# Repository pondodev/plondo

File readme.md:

# plondo

a plaid inspired 4x12 ortholinear keyboard with a rotary encoder and oled panel.

building plondo? then start at the [BOM](docs/1-bom.md)!

this is a work in progress by me, someone who is a software engineer and very much not qualified to do this kind of
thing. i'm going to do it anyway.

if you're missing symbols/footprints then make sure you run `git submodule init && git submodule update` to pull the
relevant libraries down.

this keyboard derives from the [plaid](https://github.com/hsgw/plaid) and the
[mysterium](https://github.com/coseyfannitutti/mysterium).

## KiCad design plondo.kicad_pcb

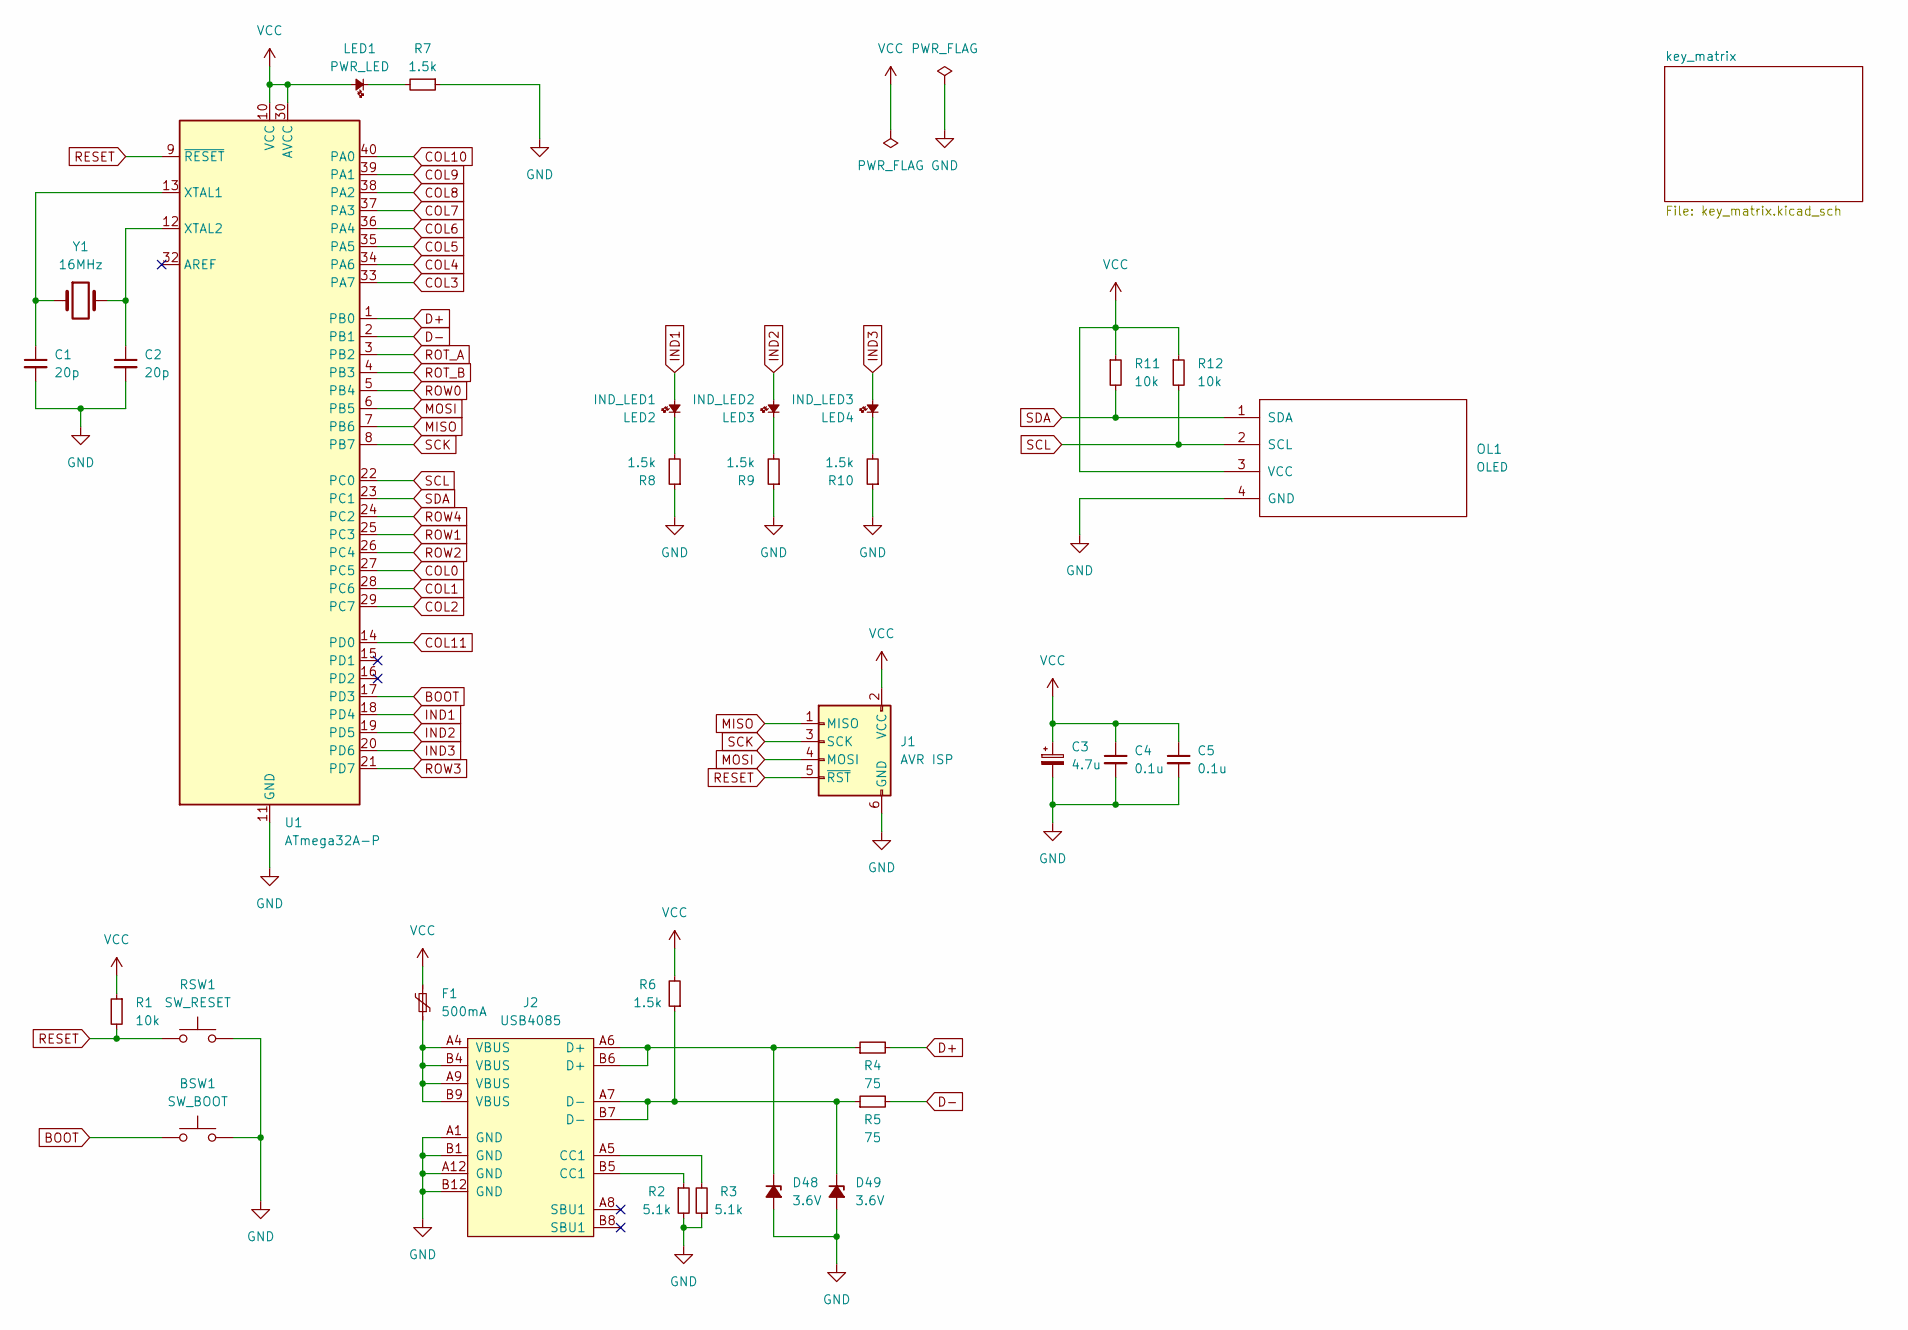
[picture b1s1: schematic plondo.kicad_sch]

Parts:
BSW1: SW_BOOT; SW_PUSH_6mm_H4.3mm
C1, C2: 20p; C_Disc_D7.5mm_W4.4mm_P5.00mm
C3: 4.7u; CP_Radial_D4.0mm_P1.50mm
C4, C5: 0.1u; C_Disc_D5.0mm_W2.5mm_P5.00mm
D48, D49: 3.6V; D_DO-35_SOD27_P7.62mm_Horizontal
F1: 500mA; Fuse_Littelfuse_395Series
J1: AVR ISP; PinHeader_2x03_P2.54mm_Vertical
J2: USB4085; Farnell 2924867
LED1: PWR_LED; LED_D3.0mm
LED2: IND_LED1; LED_D3.0mm
LED3: IND_LED2; LED_D3.0mm
LED4: IND_LED3; LED_D3.0mm
OL1: OLED; OLED_v2
R1, R11, R12: 10k; R_Axial_DIN0207_L6.3mm_D2.5mm_P7.62mm_Horizontal
R2, R3: 5.1k; R_Axial_DIN0207_L6.3mm_D2.5mm_P7.62mm_Horizontal
R4, R5: 75; R_Axial_DIN0207_L6.3mm_D2.5mm_P7.62mm_Horizontal
R6, R7, R8, R9, R10: 1.5k; R_Axial_DIN0207_L6.3mm_D2.5mm_P7.62mm_Horizontal
RSW1: SW_RESET; SW_PUSH_6mm_H4.3mm
U1: ATmega32A-P; DIP-40_W15.24mm_Socket
Y1: 16MHz; Resonator-2Pin_W10.0mm_H5.0mm

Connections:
BOOT: BSW1.1, U1.17 (PD3)
COL0: U1.27 (PC5); also elsewhere on the board
COL1: U1.28 (PC6); also elsewhere on the board
COL2: U1.29 (PC7); also elsewhere on the board
COL3: U1.33 (PA7); also elsewhere on the board
COL4: U1.34 (PA6); also elsewhere on the board
COL5: U1.35 (PA5); also elsewhere on the board
COL6: U1.36 (PA4); also elsewhere on the board
COL7: U1.37 (PA3); also elsewhere on the board
COL8: U1.38 (PA2); also elsewhere on the board
COL9: U1.39 (PA1); also elsewhere on the board
COL10: U1.40 (PA0); also elsewhere on the board
COL11: U1.14 (PD0); also elsewhere on the board
D+: R4.2, U1.1 (PB0)
D-: R5.2, U1.2 (PB1)
GND: BSW1.2, C1.2, C2.2, C3.2, C4.2, C5.2, D48.2 (A), D49.2 (A), J1.6 (GND), J2.A1 (GND), J2.A12 (GND), J2.B1 (GND), J2.B12 (GND), OL1.4 (GND), R2.2, R3.1, R7.1, R8.1, R9.1, R10.1, RSW1.2, U1.11 (GND), U1.31 (GND); also elsewhere on the board
IND1: LED2.2, U1.18 (PD4)
IND2: LED3.2, U1.19 (PD5)
IND3: LED4.2, U1.20 (PD6)
MISO: J1.1 (MISO), U1.7 (PB6)
MOSI: J1.4 (MOSI), U1.6 (PB5)
unnamed: C1.1, U1.13 (XTAL1), Y1.1
unnamed: C2.1, U1.12 (XTAL2), Y1.2
unnamed: D48.1 (K), J2.A6 (D+), J2.B6 (D+), R4.1
unnamed: D49.1 (K), J2.A7 (D-), J2.B7 (D-), R5.1, R6.1
unnamed: F1.1, J2.A4 (VBUS), J2.A9 (VBUS), J2.B4 (VBUS), J2.B9 (VBUS)
unnamed: J2.A5 (CC1), R3.2
unnamed: J2.B5 (CC1), R2.1
unnamed: LED1.1, R7.2
unnamed: LED2.1, R8.2
unnamed: LED3.1, R9.2
unnamed: LED4.1, R10.2
RESET: J1.5 (~RST), R1.2, RSW1.1, U1.9 (~RESET)
ROT_A: U1.3 (PB2); also elsewhere on the board
ROT_B: U1.4 (PB3); also elsewhere on the board
ROW0: U1.5 (PB4); also elsewhere on the board
ROW1: U1.25 (PC3); also elsewhere on the board
ROW2: U1.26 (PC4); also elsewhere on the board
ROW3: U1.21 (PD7); also elsewhere on the board
ROW4: U1.24 (PC2); also elsewhere on the board
SCK: J1.3 (SCK), U1.8 (PB7)
SCL: OL1.2 (SCL), R12.2, U1.22 (PC0)
SDA: OL1.1 (SDA), R11.2, U1.23 (PC1)
VCC: C3.1, C4.1, C5.1, F1.2, J1.2 (VCC), LED1.2, OL1.3 (VCC), R1.1, R6.2, R11.1, R12.1, U1.10 (VCC), U1.30 (AVCC)

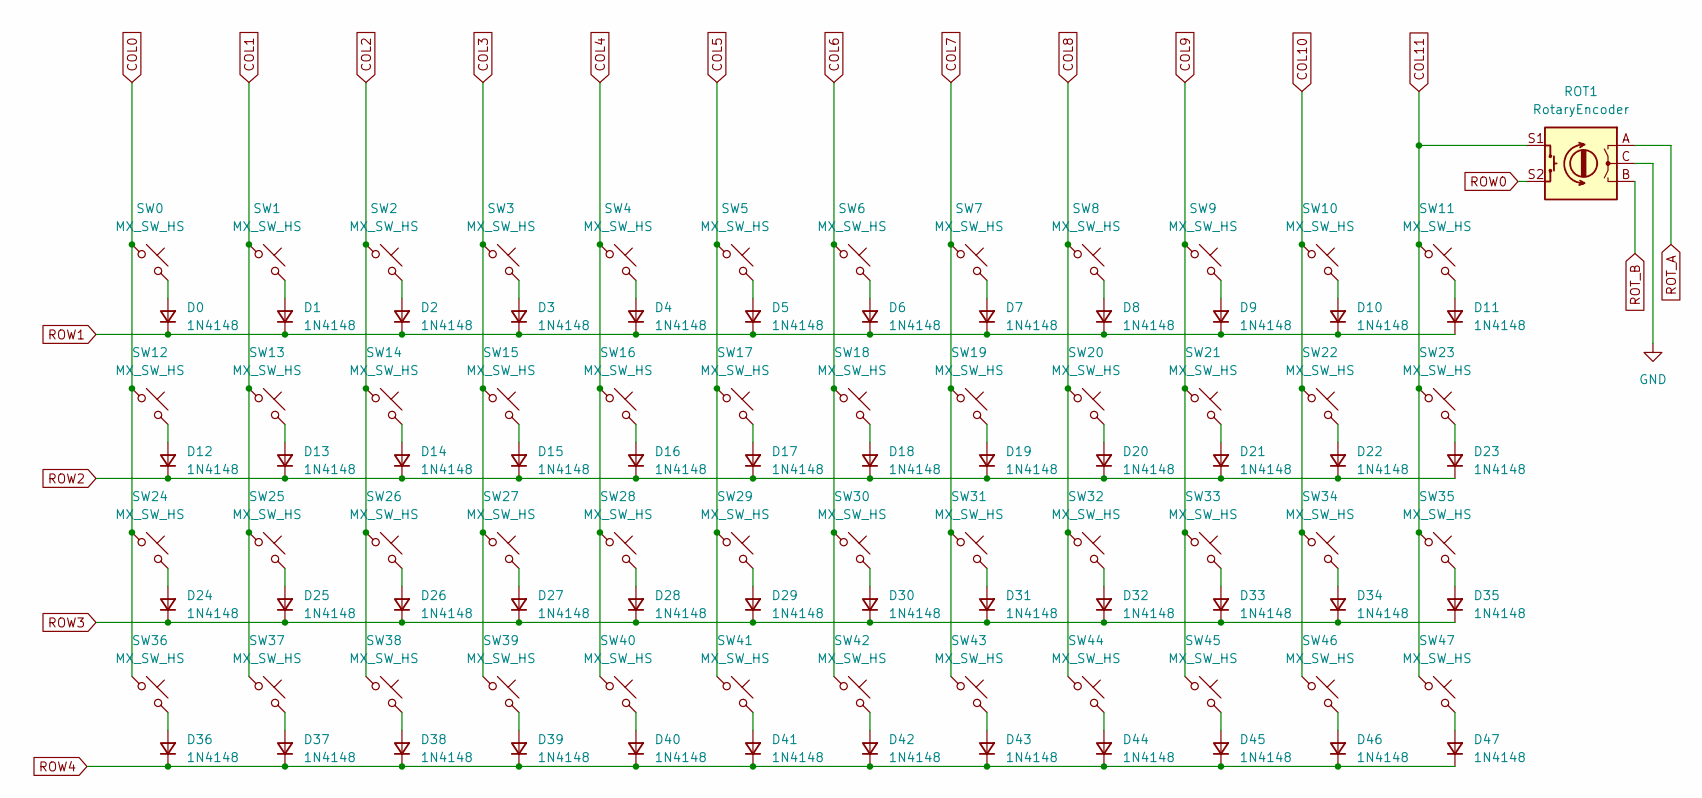
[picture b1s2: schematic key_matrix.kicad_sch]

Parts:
D0, D1, D2, D3, D4, D5, D6, D7, D8, D9, D10, D11, D12, D13, D14, D15, D16, D17, D18, D19, D20, D21, D22, D23, D24, D25, D26, D27, D28, D29, D30, D31, D32, D33, D34, D35, D36, D37, D38, D39, D40, D41, D42, D43, D44, D45, D46, D47: 1N4148; D_DO-35_SOD27_P7.62mm_Horizontal
ROT1: RotaryEncoder; RotaryEncoder_Alps_EC11E-Switch_Vertical_H20mm
SW0, SW1, SW2, SW3, SW4, SW5, SW6, SW7, SW8, SW9, SW10, SW11, SW12, SW13, SW14, SW15, SW16, SW17, SW18, SW19, SW20, SW21, SW22, SW23, SW24, SW25, SW26, SW27, SW28, SW29, SW30, SW31, SW32, SW33, SW34, SW35, SW36, SW37, SW38, SW39, SW40, SW41, SW42, SW43, SW44, SW45, SW46, SW47: MX_SW_HS; SW_MX_HS_1u

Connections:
COL0: SW0.1, SW12.1, SW24.1, SW36.1; also elsewhere on the board
COL1: SW1.1, SW13.1, SW25.1, SW37.1; also elsewhere on the board
COL2: SW2.1, SW14.1, SW26.1, SW38.1; also elsewhere on the board
COL3: SW3.1, SW15.1, SW27.1, SW39.1; also elsewhere on the board
COL4: SW4.1, SW16.1, SW28.1, SW40.1; also elsewhere on the board
COL5: SW5.1, SW17.1, SW29.1, SW41.1; also elsewhere on the board
COL6: SW6.1, SW18.1, SW30.1, SW42.1; also elsewhere on the board
COL7: SW7.1, SW19.1, SW31.1, SW43.1; also elsewhere on the board
COL8: SW8.1, SW20.1, SW32.1, SW44.1; also elsewhere on the board
COL9: SW9.1, SW21.1, SW33.1, SW45.1; also elsewhere on the board
COL10: SW10.1, SW22.1, SW34.1, SW46.1; also elsewhere on the board
COL11: ROT1.S1, SW11.1, SW23.1, SW35.1, SW47.1; also elsewhere on the board
GND: ROT1.C; also elsewhere on the board
unnamed: D0.2 (A), SW0.2
unnamed: D1.2 (A), SW1.2
unnamed: D2.2 (A), SW2.2
unnamed: D3.2 (A), SW3.2
unnamed: D4.2 (A), SW4.2
unnamed: D5.2 (A), SW5.2
unnamed: D6.2 (A), SW6.2
unnamed: D7.2 (A), SW7.2
unnamed: D8.2 (A), SW8.2
unnamed: D9.2 (A), SW9.2
unnamed: D10.2 (A), SW10.2
unnamed: D11.2 (A), SW11.2
unnamed: D12.2 (A), SW12.2
unnamed: D13.2 (A), SW13.2
unnamed: D14.2 (A), SW14.2
unnamed: D15.2 (A), SW15.2
unnamed: D16.2 (A), SW16.2
unnamed: D17.2 (A), SW17.2
unnamed: D18.2 (A), SW18.2
unnamed: D19.2 (A), SW19.2
unnamed: D20.2 (A), SW20.2
unnamed: D21.2 (A), SW21.2
unnamed: D22.2 (A), SW22.2
unnamed: D23.2 (A), SW23.2
unnamed: D24.2 (A), SW24.2
unnamed: D25.2 (A), SW25.2
unnamed: D26.2 (A), SW26.2
unnamed: D27.2 (A), SW27.2
unnamed: D28.2 (A), SW28.2
unnamed: D29.2 (A), SW29.2
unnamed: D30.2 (A), SW30.2
unnamed: D31.2 (A), SW31.2
unnamed: D32.2 (A), SW32.2
unnamed: D33.2 (A), SW33.2
unnamed: D34.2 (A), SW34.2
unnamed: D35.2 (A), SW35.2
unnamed: D36.2 (A), SW36.2
unnamed: D37.2 (A), SW37.2
unnamed: D38.2 (A), SW38.2
unnamed: D39.2 (A), SW39.2
unnamed: D40.2 (A), SW40.2
unnamed: D41.2 (A), SW41.2
unnamed: D42.2 (A), SW42.2
unnamed: D43.2 (A), SW43.2
unnamed: D44.2 (A), SW44.2
unnamed: D45.2 (A), SW45.2
unnamed: D46.2 (A), SW46.2
unnamed: D47.2 (A), SW47.2
ROT_A: ROT1.A; also elsewhere on the board
ROT_B: ROT1.B; also elsewhere on the board
ROW0: ROT1.S2; also elsewhere on the board
ROW1: D0.1 (K), D1.1 (K), D2.1 (K), D3.1 (K), D4.1 (K), D5.1 (K), D6.1 (K), D7.1 (K), D8.1 (K), D9.1 (K), D10.1 (K), D11.1 (K); also elsewhere on the board
ROW2: D12.1 (K), D13.1 (K), D14.1 (K), D15.1 (K), D16.1 (K), D17.1 (K), D18.1 (K), D19.1 (K), D20.1 (K), D21.1 (K), D22.1 (K), D23.1 (K); also elsewhere on the board
ROW3: D24.1 (K), D25.1 (K), D26.1 (K), D27.1 (K), D28.1 (K), D29.1 (K), D30.1 (K), D31.1 (K), D32.1 (K), D33.1 (K), D34.1 (K), D35.1 (K); also elsewhere on the board
ROW4: D36.1 (K), D37.1 (K), D38.1 (K), D39.1 (K), D40.1 (K), D41.1 (K), D42.1 (K), D43.1 (K), D44.1 (K), D45.1 (K), D46.1 (K), D47.1 (K); also elsewhere on the board

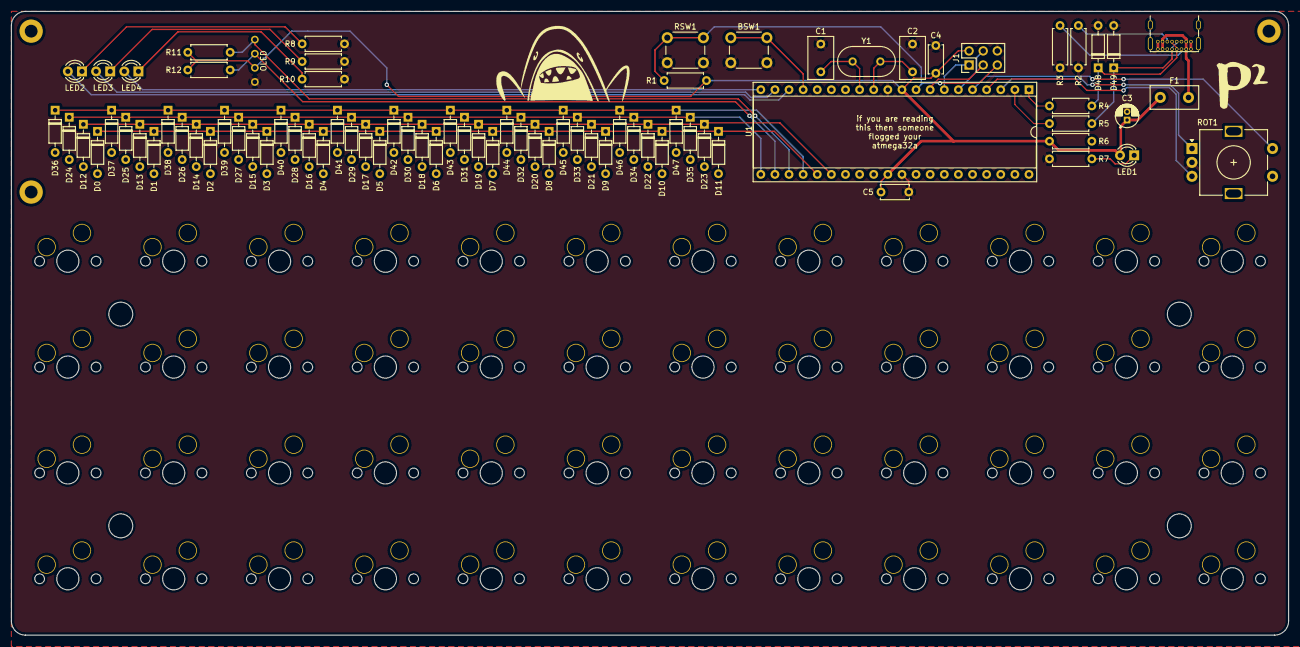
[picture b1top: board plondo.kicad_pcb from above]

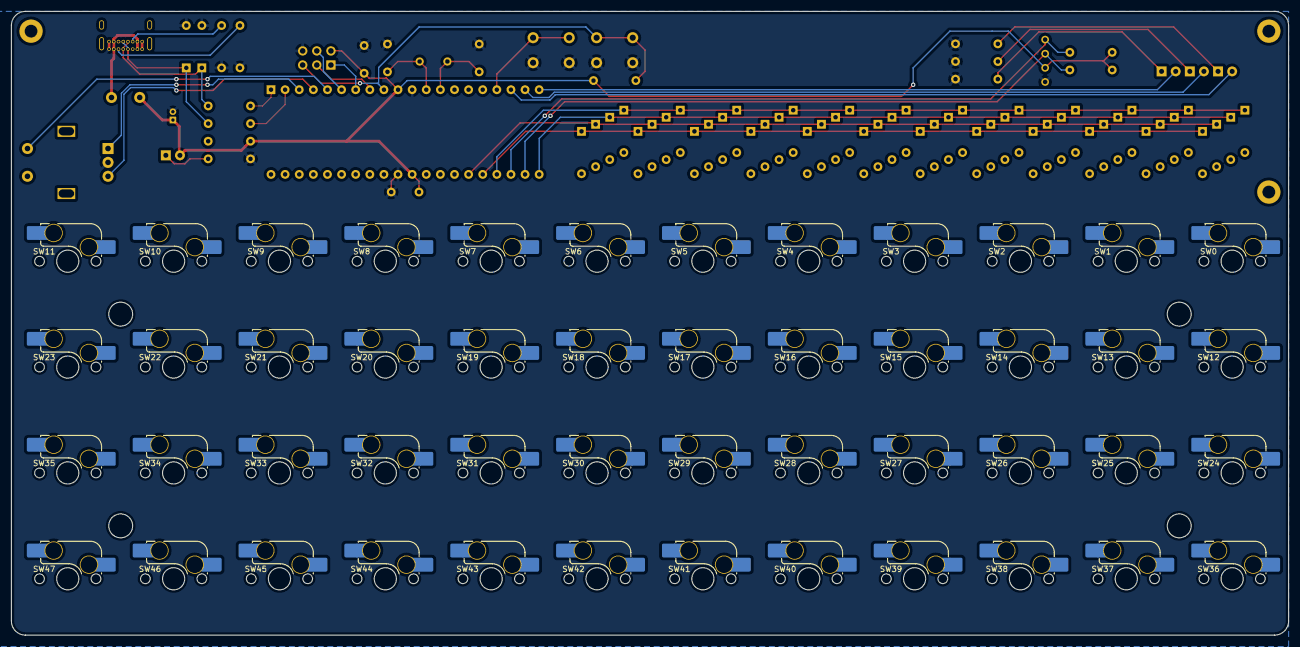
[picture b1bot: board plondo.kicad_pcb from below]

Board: 2 copper layers, 229.9 x 112.2 mm, 132 parts (48 on the bottom side), 92 nets.

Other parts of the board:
Ref**: Val**; spacer_m2
Ref**#2, Ref**#3, Ref**#4: Val**; spacer_m2

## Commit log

2022-07-29 add readme
2022-07-29 add libs as submodules, fix up usb c wiring
2022-07-30 complete main circuitry
2022-07-31 add indicator LEDs
2022-07-31 add missing connections + oled
2022-07-31 first pass of pcb layout, fix footprints
2022-07-31 add pullups for i2c lines
2022-07-31 edited schematics for clarity, position more of pcb
2022-07-31 position all components on the pcb
2022-08-02 rearrange pins + misc pcb arrangement fixes
2022-08-02 bunch of routing done
2022-08-03 add license
2022-08-03 finish connecting rows to diodes
2022-08-03 start redoing my awful routing
2022-08-04 complete connecting key matrix
2022-08-04 a lot more connections
2022-08-05 connected all components on the pcb
2022-08-07 rounded corners!
2022-08-07 add nice silkscreen stuff, update readme
2022-08-07 add ground planes, make vcc lines thicker
2022-08-08 rearrange silkscreen references
2022-08-08 add mounting holes, vias for ground planes
2022-08-08 stub out documentation pages
2022-08-08 update bootloader guide
2022-08-08 add bom
2022-08-08 add barebones baseplate
2022-08-09 add switchplate
2022-08-17 remove round tracks config
2022-08-17 resize ground plane zones, update pcb image
2022-08-17 connect all diodes
2022-08-17 connect last of the components
2022-08-17 update switchplate
2022-08-17 add ground plane vias
2022-08-17 edit baseplate
2022-08-17 route most everything that isn't the key matrix
2022-08-17 move everything into place on the new pcb size
2022-08-17 resize board
2022-08-17 move some components around
